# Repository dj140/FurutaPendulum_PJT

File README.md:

# FurutaPendulum_PJT

https://user-images.githubusercontent.com/33819388/154991899-b6fe6e4b-3fc9-4029-be56-d972ed57666c.mp4

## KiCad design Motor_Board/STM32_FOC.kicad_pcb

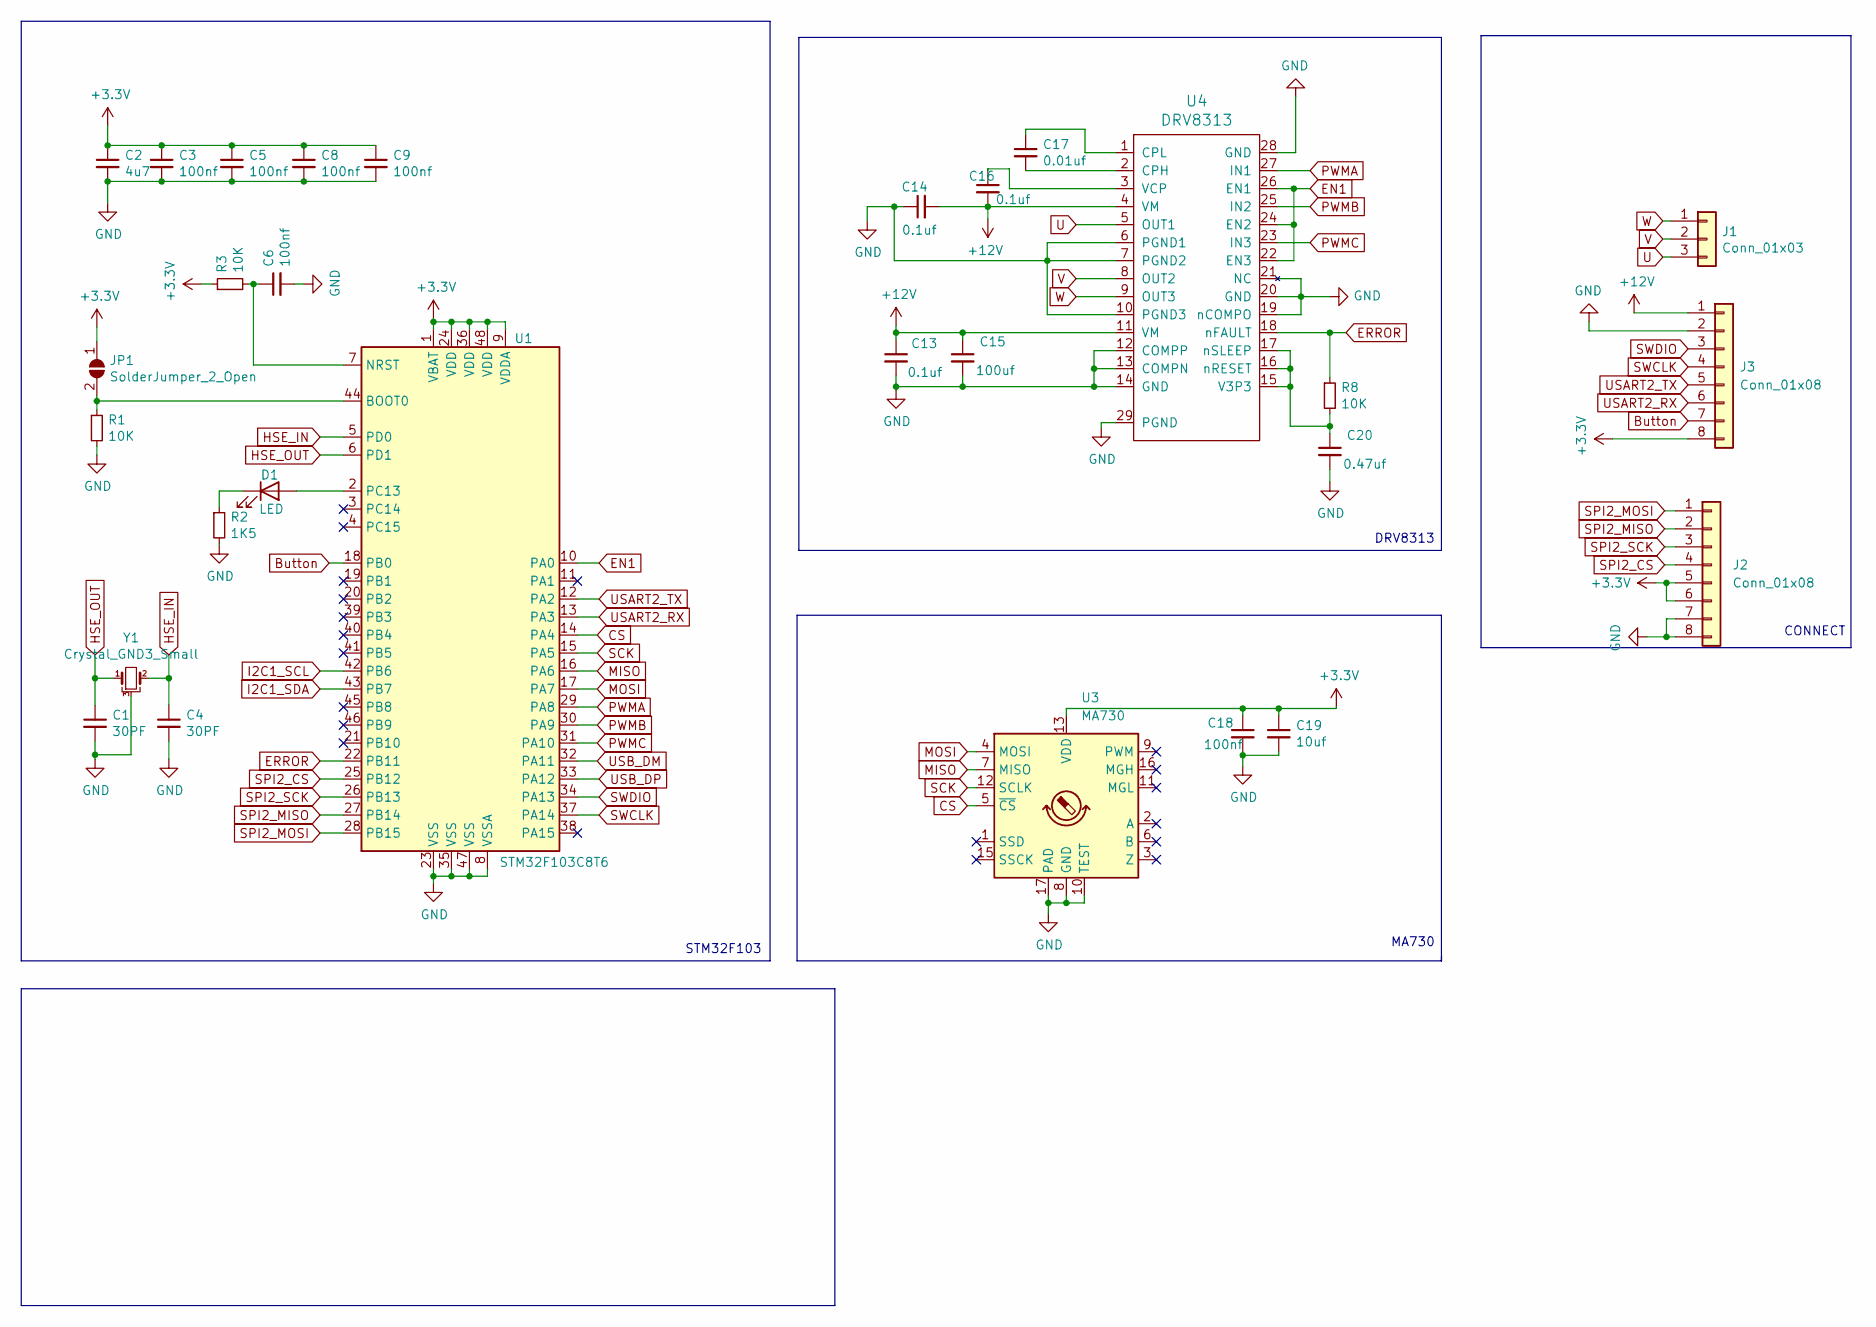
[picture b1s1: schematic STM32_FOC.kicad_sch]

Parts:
C1, C4: 30PF; C_0402_1005Metric
C2: 4u7; C_0402_1005Metric
C3, C5, C6, C8, C9, C18: 100nf; C_0402_1005Metric
C13: 0.1uf; C_0603_1608Metric
C14, C16: 0.1uf; C_0402_1005Metric
C15: 100uf; C_1206_3216Metric
C17: 0.01uf; C_0402_1005Metric
C19: 10uf; C_0402_1005Metric
C20: 0.47uf; C_0402_1005Metric
D1: LED; LED_0402_1005Metric
J1: Conn_01x03; Molex_PicoBlade_53047-0310_1x03_P1.25mm_Vertical
J2: Conn_01x08; JST_SH_BM08B-SRSS-TB_1x08-1MP_P1.00mm_Vertical
J3: Conn_01x08; Molex_PicoBlade_53047-0810_1x08_P1.25mm_Vertical
JP1: SolderJumper_2_Open; SoldJumper-2-P0.5mm_Open_RoundedPad
R1, R3, R8: 10K; R_0402_1005Metric
R2: 1K5; R_0402_1005Metric
U1: STM32F103C8T6; LQFP-48_7x7mm_P0.5mm
U3: MA730; QFN-16-1EP_3x3mm_P0.5mm_EP1.75x1.75mm
U4: DRV8313; IC_TPS61196PWPRQ1
Y1: Crystal_GND3_Small; CSTCE8M00G55-R0

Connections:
+3V3: C2.1, C3.1, C5.1, C8.1, C9.1, C18.1, C19.1, J2.5, J2.6, J3.8, JP1.1 (A), R3.1, U1.1 (VBAT), U1.9 (VDDA), U1.24 (VDD), U1.36 (VDD), U1.48 (VDD), U3.13 (VDD)
+12V: C13.1, C14.2, C15.1, C16.2, J3.1, U4.4 (VM), U4.11 (VM)
Button: J3.7, U1.18 (PB0)
CS: U1.14 (PA4), U3.5 (~CS)
EN1: U1.10 (PA0), U4.22 (EN3), U4.24 (EN2), U4.26 (EN1)
ERROR: R8.1, U1.22 (PB11), U4.18 (nFAULT)
GND: C1.2, C2.2, C3.2, C4.2, C5.2, C6.2, C8.2, C9.2, C13.2, C14.1, C15.2, C18.2, C19.2, C20.2, J2.7, J2.8, J3.2, R1.2, R2.2, U1.8 (VSSA), U1.23 (VSS), U1.35 (VSS), U1.47 (VSS), U3.8 (GND), U3.10 (TEST), U3.17 (PAD), U4.6 (PGND1), U4.7 (PGND2), U4.10 (PGND3), U4.12 (COMPP), U4.13 (COMPN), U4.14 (GND), U4.19 (nCOMPO), U4.20 (GND), U4.21 (NC), U4.28 (GND), U4.29 (PGND), U4.30, U4.31, U4.34, U4.41, U4.42, U4.43, U4.44, U4.45, U4.46, Y1.3
HSE_IN: C4.1, U1.5 (PD0), Y1.2
HSE_OUT: C1.1, U1.6 (PD1), Y1.1
I2C1_SCL: U1.42 (PB6)
I2C1_SDA: U1.43 (PB7)
MISO: U1.16 (PA6), U3.7 (MISO)
MOSI: U1.17 (PA7), U3.4 (MOSI)
unnamed: C6.1, R3.2, U1.7 (NRST)
unnamed: C16.1, U4.3 (VCP)
unnamed: C17.1, U4.1 (CPL)
unnamed: C17.2, U4.2 (CPH)
unnamed: C20.1, R8.2, U4.15 (V3P3), U4.16 (nRESET), U4.17 (nSLEEP)
unnamed: D1.1 (K), R2.1
unnamed: D1.2 (A), U1.2 (PC13)
unnamed: JP1.2 (B), R1.1, U1.44 (BOOT0)
PWMA: U1.29 (PA8), U4.27 (IN1)
PWMB: U1.30 (PA9), U4.25 (IN2)
PWMC: U1.31 (PA10), U4.23 (IN3)
SCK: U1.15 (PA5), U3.12 (SCLK)
SPI2_CS: J2.4, U1.25 (PB12)
SPI2_MISO: J2.2, U1.27 (PB14)
SPI2_MOSI: J2.1, U1.28 (PB15)
SPI2_SCK: J2.3, U1.26 (PB13)
SWCLK: J3.4, U1.37 (PA14)
SWDIO: J3.3, U1.34 (PA13)
U: J1.3, U4.5 (OUT1)
USART2_RX: J3.6, U1.13 (PA3)
USART2_TX: J3.5, U1.12 (PA2)
USB_DM: U1.32 (PA11)
USB_DP: U1.33 (PA12)
V: J1.2, U4.8 (OUT2)
W: J1.1, U4.9 (OUT3)

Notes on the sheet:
MA730
STM32F103
CONNECT
DRV8313

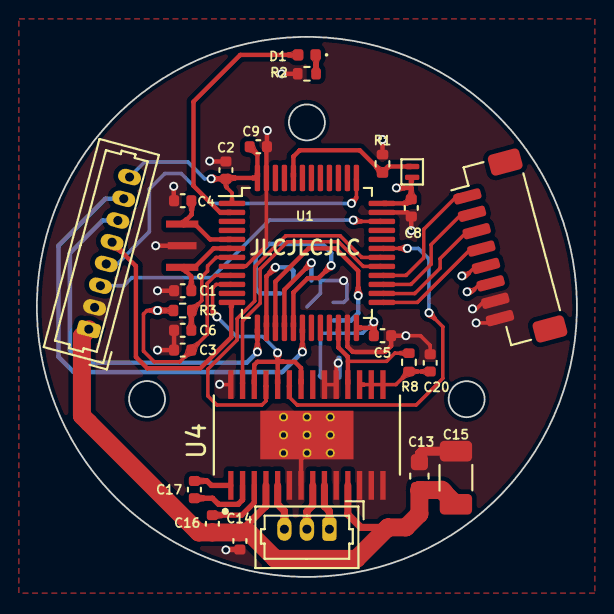
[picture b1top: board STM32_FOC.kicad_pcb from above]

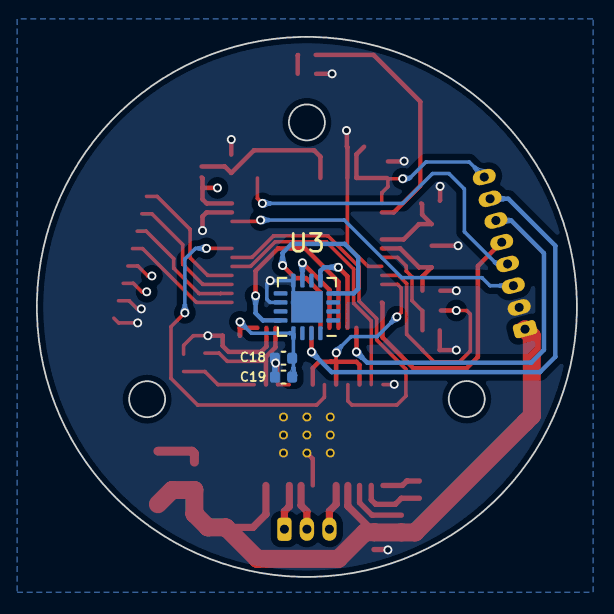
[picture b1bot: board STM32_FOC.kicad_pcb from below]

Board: 4 copper layers, 30.0 x 30.0 mm, 29 parts (3 on the bottom side), 34 nets.

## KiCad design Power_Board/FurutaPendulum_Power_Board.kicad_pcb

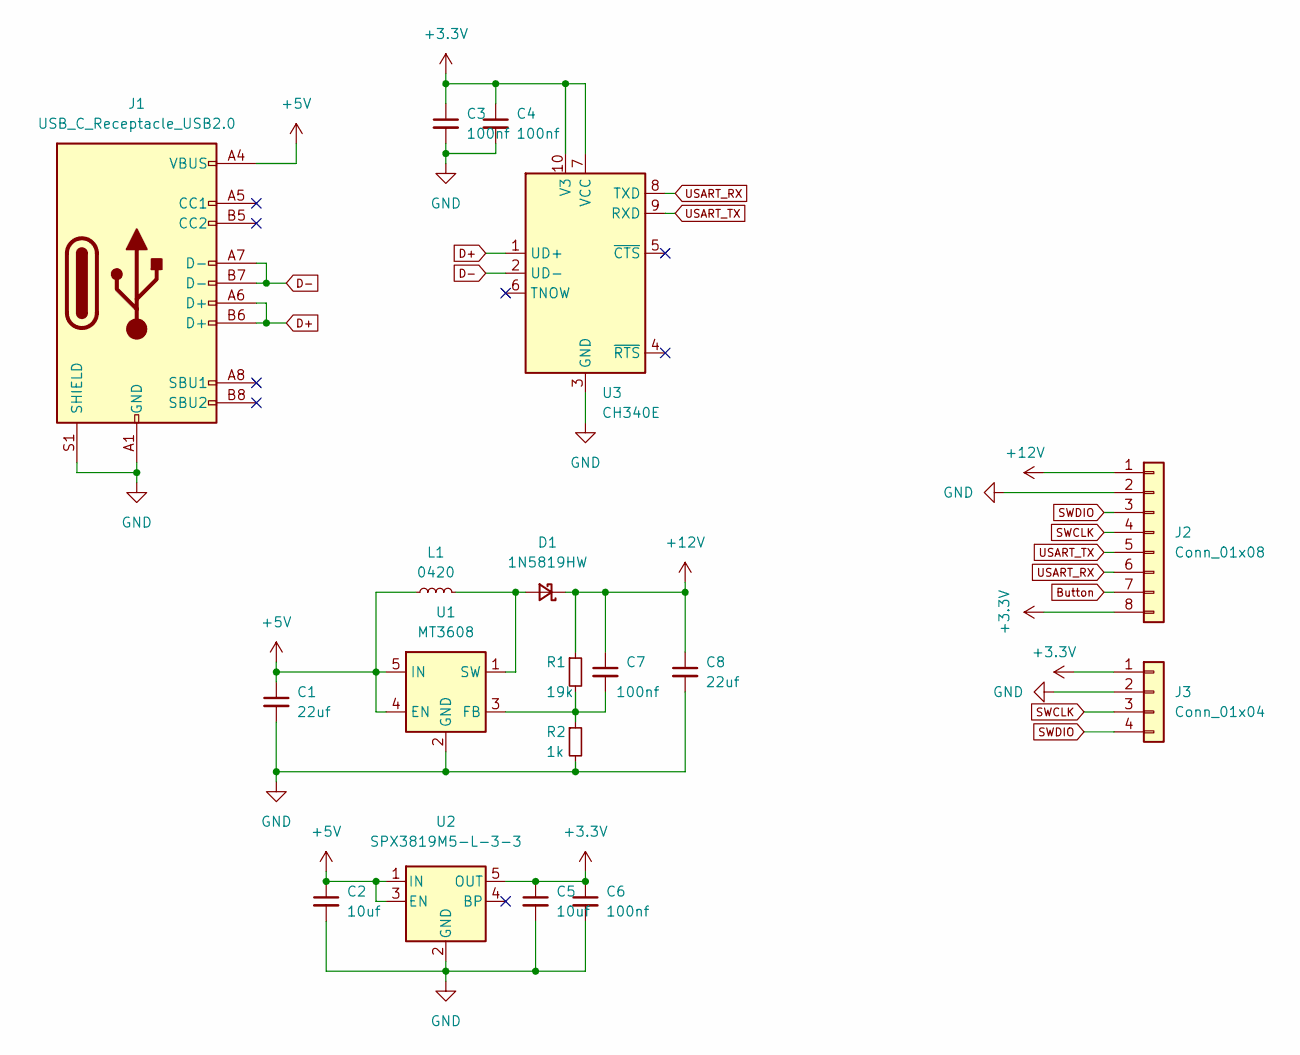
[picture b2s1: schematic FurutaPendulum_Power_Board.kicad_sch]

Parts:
C1, C8: 22uf; C_1206_3216Metric
C2, C5: 10uf; C_0402_1005Metric_Pad0.74x0.62mm_HandSolder
C3, C4, C6, C7: 100nf; C_0402_1005Metric_Pad0.74x0.62mm_HandSolder
D1: 1N5819HW; D_SOD-123
J1: USB_C_Receptacle_USB2.0; USB_C_Receptacle_HRO_TYPE-C-31-M-12
J2: Conn_01x08; Molex_PicoBlade_53048-0810_1x08_P1.25mm_Horizontal
J3: Conn_01x04; Molex_PicoBlade_53048-0410_1x04_P1.25mm_Horizontal
L1: 0420; L_0420
R1: 19k; R_0402_1005Metric_Pad0.72x0.64mm_HandSolder
R2: 1k; R_0402_1005Metric_Pad0.72x0.64mm_HandSolder
U1: MT3608; SOT-23-6
U2: SPX3819M5-L-3-3; SOT-23-5
U3: CH340E; MSOP-10_3x3mm_P0.5mm

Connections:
+3V3: C3.1, C4.1, C5.1, C6.1, J2.8, J3.1, U2.5 (OUT), U3.7 (VCC), U3.10 (V3)
+5V: C1.1, C2.1, J1.A4 (VBUS), J1.A9 (VBUS), J1.B4 (VBUS), J1.B9 (VBUS), L1.1, U1.4 (EN), U1.5 (IN), U2.1 (IN), U2.3 (EN)
+12V: C7.1, C8.1, D1.1 (K), J2.1, R1.1
Button: J2.7
D+: J1.A6 (D+), J1.B6 (D+), U3.1 (UD+)
D-: J1.A7 (D-), J1.B7 (D-), U3.2 (UD-)
GND: C1.2, C2.2, C3.2, C4.2, C5.2, C6.2, C8.2, J1.A1 (GND), J1.A12 (GND), J1.B1 (GND), J1.B12 (GND), J1.S1 (SHIELD), J2.2, J3.2, R2.2, U1.2 (GND), U2.2 (GND), U3.3 (GND)
unnamed: C7.2, R1.2, R2.1, U1.3 (FB)
unnamed: D1.2 (A), L1.2, U1.1 (SW)
SWCLK: J2.4, J3.3
SWDIO: J2.3, J3.4
USART_RX: J2.6, U3.8 (TXD)
USART_TX: J2.5, U3.9 (RXD)

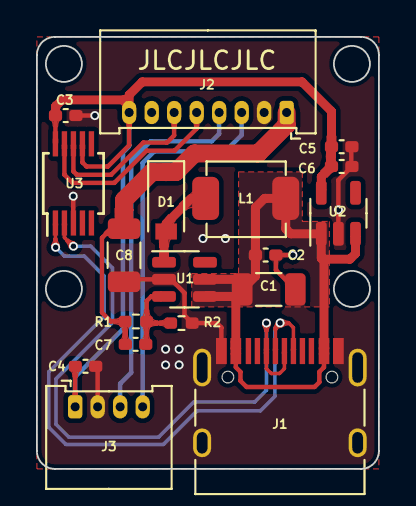
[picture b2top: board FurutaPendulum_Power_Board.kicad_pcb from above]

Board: 4 copper layers, 19.0 x 24.0 mm, 18 parts (0 on the bottom side), 12 nets.

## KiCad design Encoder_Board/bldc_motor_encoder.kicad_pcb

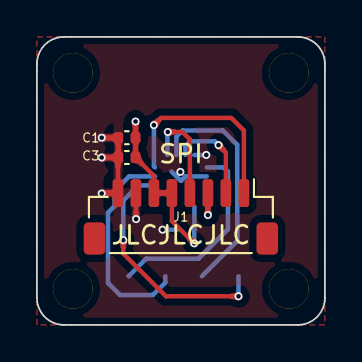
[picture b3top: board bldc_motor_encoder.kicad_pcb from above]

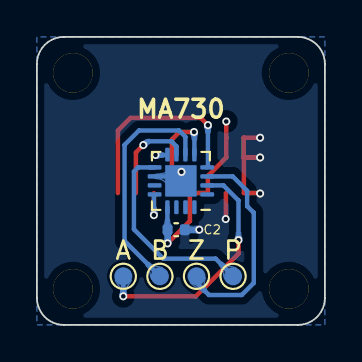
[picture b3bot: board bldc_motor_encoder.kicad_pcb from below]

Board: 4 copper layers, 16.0 x 16.0 mm, 13 parts (6 on the bottom side), 10 nets.

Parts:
A: TestPoint_Small; TestPoint_Pad_D1.0mm
B: TestPoint_Small; TestPoint_Pad_D1.0mm
C1: 1uF; C_0402_1005Metric
C2, C3: 100nF; C_0402_1005Metric
H1, H2, H3, H4: MountingHole; MountingHole_2.2mm_M2
J1: Conn_01x08; JST_SH_BM08B-SRSS-TB_1x08-1MP_P1.00mm_Vertical
P: TestPoint_Small; TestPoint_Pad_D1.0mm
U1: MA730; QFN-16-1EP_3x3mm_P0.5mm_EP1.75x1.75mm
Z: TestPoint_Small; TestPoint_Pad_D1.0mm

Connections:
+3V3: C1.1, C2.1, C3.1, J1.5, J1.6, U1.13 (VDD)
GND: C1.2, C2.2, C3.2, J1.7, J1.8, U1.8 (GND), U1.10 (TEST), U1.17 (PAD)
unnamed: A.1, U1.2 (A)
unnamed: B.1, U1.6 (B)
unnamed: J1.1, U1.4 (MOSI)
unnamed: J1.2, U1.7 (MISO)
unnamed: J1.3, U1.12 (SCLK)
unnamed: J1.4, U1.5 (~CS)
unnamed: P.1, U1.9 (PWM)
unnamed: U1.3 (Z), Z.1

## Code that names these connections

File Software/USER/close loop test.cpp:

#include "Arduino.h"
#define LED_PIN PC13
//#include "BLDCMotor.h"
//#include "sensors/MagneticSensorI2C.h"
//#include "drivers/BLDCDriver3PWM.h"



/**
 *
 * Position/angle motion control example
 * Steps:
 * 1) Configure the motor and magnetic sensor
 * 2) Run the code
 * 3) Set the target angle (in radians) from serial terminal
 *
 */
#include <SimpleFOC.h>

// magnetic sensor instance - SPI
//MagneticSensorSPI sensor = MagneticSensorSPI(MA730_SPI, PA4);

MagneticSensorSPI sensor = MagneticSensorSPI(MA730_SPI, PA4);

// magnetic sensor instance - MagneticSensorI2C
//MagneticSensorI2C sensor = MagneticSensorI2C(AS5600_I2C);


// BLDC motor & driver instance
BLDCMotor motor = BLDCMotor(7);
BLDCDriver3PWM driver = BLDCDriver3PWM(PA8, PA9, PA10, PA11);

// Stepper motor & driver instance
//StepperMotor motor = StepperMotor(50);
//StepperDriver4PWM driver = StepperDriver4PWM(9, 5, 10, 6,  8);

// angle set point variable
float target_angle = 0;
// instantiate the commander
Commander command = Commander(Serial2);
void doTarget(char* cmd) { command.scalar(&target_angle, cmd); }

void setup() {
  pinMode(PC13, OUTPUT);
  // initialise magnetic sensor hardware
  sensor.init();
  // link the motor to the sensor
  motor.linkSensor(&sensor);

  // driver config
  // power supply voltage [V]
  driver.voltage_power_supply = 12;
  driver.init();
  // link the motor and the driver
  motor.linkDriver(&driver);

  // choose FOC modulation (optional)
  motor.foc_modulation = FOCModulationType::SpaceVectorPWM;

  // set motion control loop to be used
  motor.controller = MotionControlType::angle;

  // contoller configuration
  // default parameters in defaults.h
  // velocity PI controller parameters
  motor.PID_velocity.P = 0.15;
  motor.PID_velocity.I = 2;
  motor.PID_velocity.D = 0.0000003;
  motor.LPF_velocity.Tf = 0.05;
  motor.P_angle.P = 14;
  motor.velocity_limit = 50;
  //motor.voltage_limit = 4;

  // velocity low pass filtering time constant
  // the lower the less filtered
  //motor.LPF_velocity.Tf = 0.01f;

  // angle P controller
  //motor.P_angle.P = 20;
  // maximal velocity of the position control
  //motor.velocity_limit = 20;

  // use monitoring with serial
  Serial2.begin(115200);
  // comment out if not needed
  motor.useMonitoring(Serial2);


  // initialize motor
  motor.init();
  // align sensor and start FOC
  motor.initFOC();
  digitalWrite(PC13, HIGH);

  // add target command T
  command.add('T', doTarget, "target angle");

  Serial2.println(F("Motor ready."));
  Serial2.println(F("Set the target angle using serial terminal:"));
  _delay(1000);
}


void loop() {

  // main FOC algorithm function
  // the faster you run this function the better
  // Arduino UNO loop  ~1kHz
  // Bluepill loop ~10kHz
  motor.loopFOC();
 // Serial2.println(sensor.getAngle());
// _delay(10);
  // Motion control function
  // velocity, position or voltage (defined in motor.controller)
  // this function can be run at much lower frequency than loopFOC() function
  // You can also use motor.move() and set the motor.target in the code
  motor.move(target_angle);
Serial2.print(sensor.getAngle());
  Serial2.print("\t");
  // function intended to be used with serial plotter to monitor motor variables
  // significantly slowing the execution down!!!!
   motor.monitor();
  // user communication
  command.run();
}

/**
  * @brief  Main Function
  * @param  None
  * @retval None
  */
int main(void)
{
    NVIC_PriorityGroupConfig(NVIC_PriorityGroup_2);
    GPIO_JTAG_Disable();
    //SysClock_Init(F_CPU_128MHz);
    Delay_Init();
    ADCx_Init(ADC1);
    setup();
    for(;;)loop();
}

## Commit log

2022-02-07 version_1.0
2022-02-21 upload software
2022-02-21 add gitignore
2022-02-21 add images
